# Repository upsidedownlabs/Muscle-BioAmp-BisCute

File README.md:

# Muscle BioAmp BisCute

[-white)](https://store.upsidedownlabs.tech/product/muscle-bioamp-biscute-diy/)

Muscle BioAmp BisCute is a cute DIY EMG sensor for precise ElectroMyoGraphy (EMG) at an affordable cost. It comes with a fixed gain of x2420 and BandPass filter of 72Hz - 720Hz. To record the EMG signals you can use any standalone ADC like ADS1115 or any microcontroller development board with an ADC of your choice like Arduino UNO/Nano.

## Hardware

Muscle BioAmp Biscute has been created using KiCad and all the design files can be found under [hardware](hardware/) folder. Images below shows a quick overview of the hardware design.

| PCB Front           |  PCB Back |
| :-------------------------: | :-------------------------: |
|   |  |

### Assembly

You can get your own Muscle BioAmp BisCute bag of parts from [our store](https://store.upsidedownlabs.tech/product/muscle-bioamp-biscute-diy/) or [Tindie](https://www.tindie.com/products/upsidedownlabs/muscle-bioamp-biscute-diy-muscle-sensor/) and for assembling your Biscute you can take a look at [this interactive BOM](https://upsidedownlabs.github.io/Muscle-BioAmp-BisCute/) or the step by step guide below. 

| Step 1 - Bare board | Step 2 - 100K Resistor | Step 3 - 10K Resistor| Step 4 - 1M Resistor|
| :----: | :----: | :----: | :----: |
| ||||

| Step 5 - 330R Resistor | Step 6 - 220K Resistor | Step 7 - 4.7nF Capacitor | Step 8 - 2.2uF Capacitor |
| :----: | :----: | :----: | :----: |
| ||||

| Step 9 - 470uF Capacitor | Step 10 - 100nF Capacitor | Step 11 - 1nF Capacitor | Step 13 - 1K Resistor |
| :----: | :----: | :----: | :----: |
| ||||

| Step 13 - BioAmp Connector | Step 14 - Header Pin | Step 15 - IC | Step 16 - Biscute ready |
| :----: | :----: | :----: | :----: |
| ||||

## License

| Licenses Facts              |  OSHWA Certification |
| :-------------------------: | :-------------------------: |
|   |  | 

#### Hardware
CERN Open Hardware License Version 2 - Strongly Reciprocal ([CERN-OHL-S-2.0](https://spdx.org/licenses/CERN-OHL-S-2.0.html)).

#### Software
MIT open source [license](http://opensource.org/licenses/MIT).

#### Documentation:
<br />This work is licensed under a <a rel="license" href="http://creativecommons.org/licenses/by/4.0/">Creative Commons Attribution 4.0 International License</a>.

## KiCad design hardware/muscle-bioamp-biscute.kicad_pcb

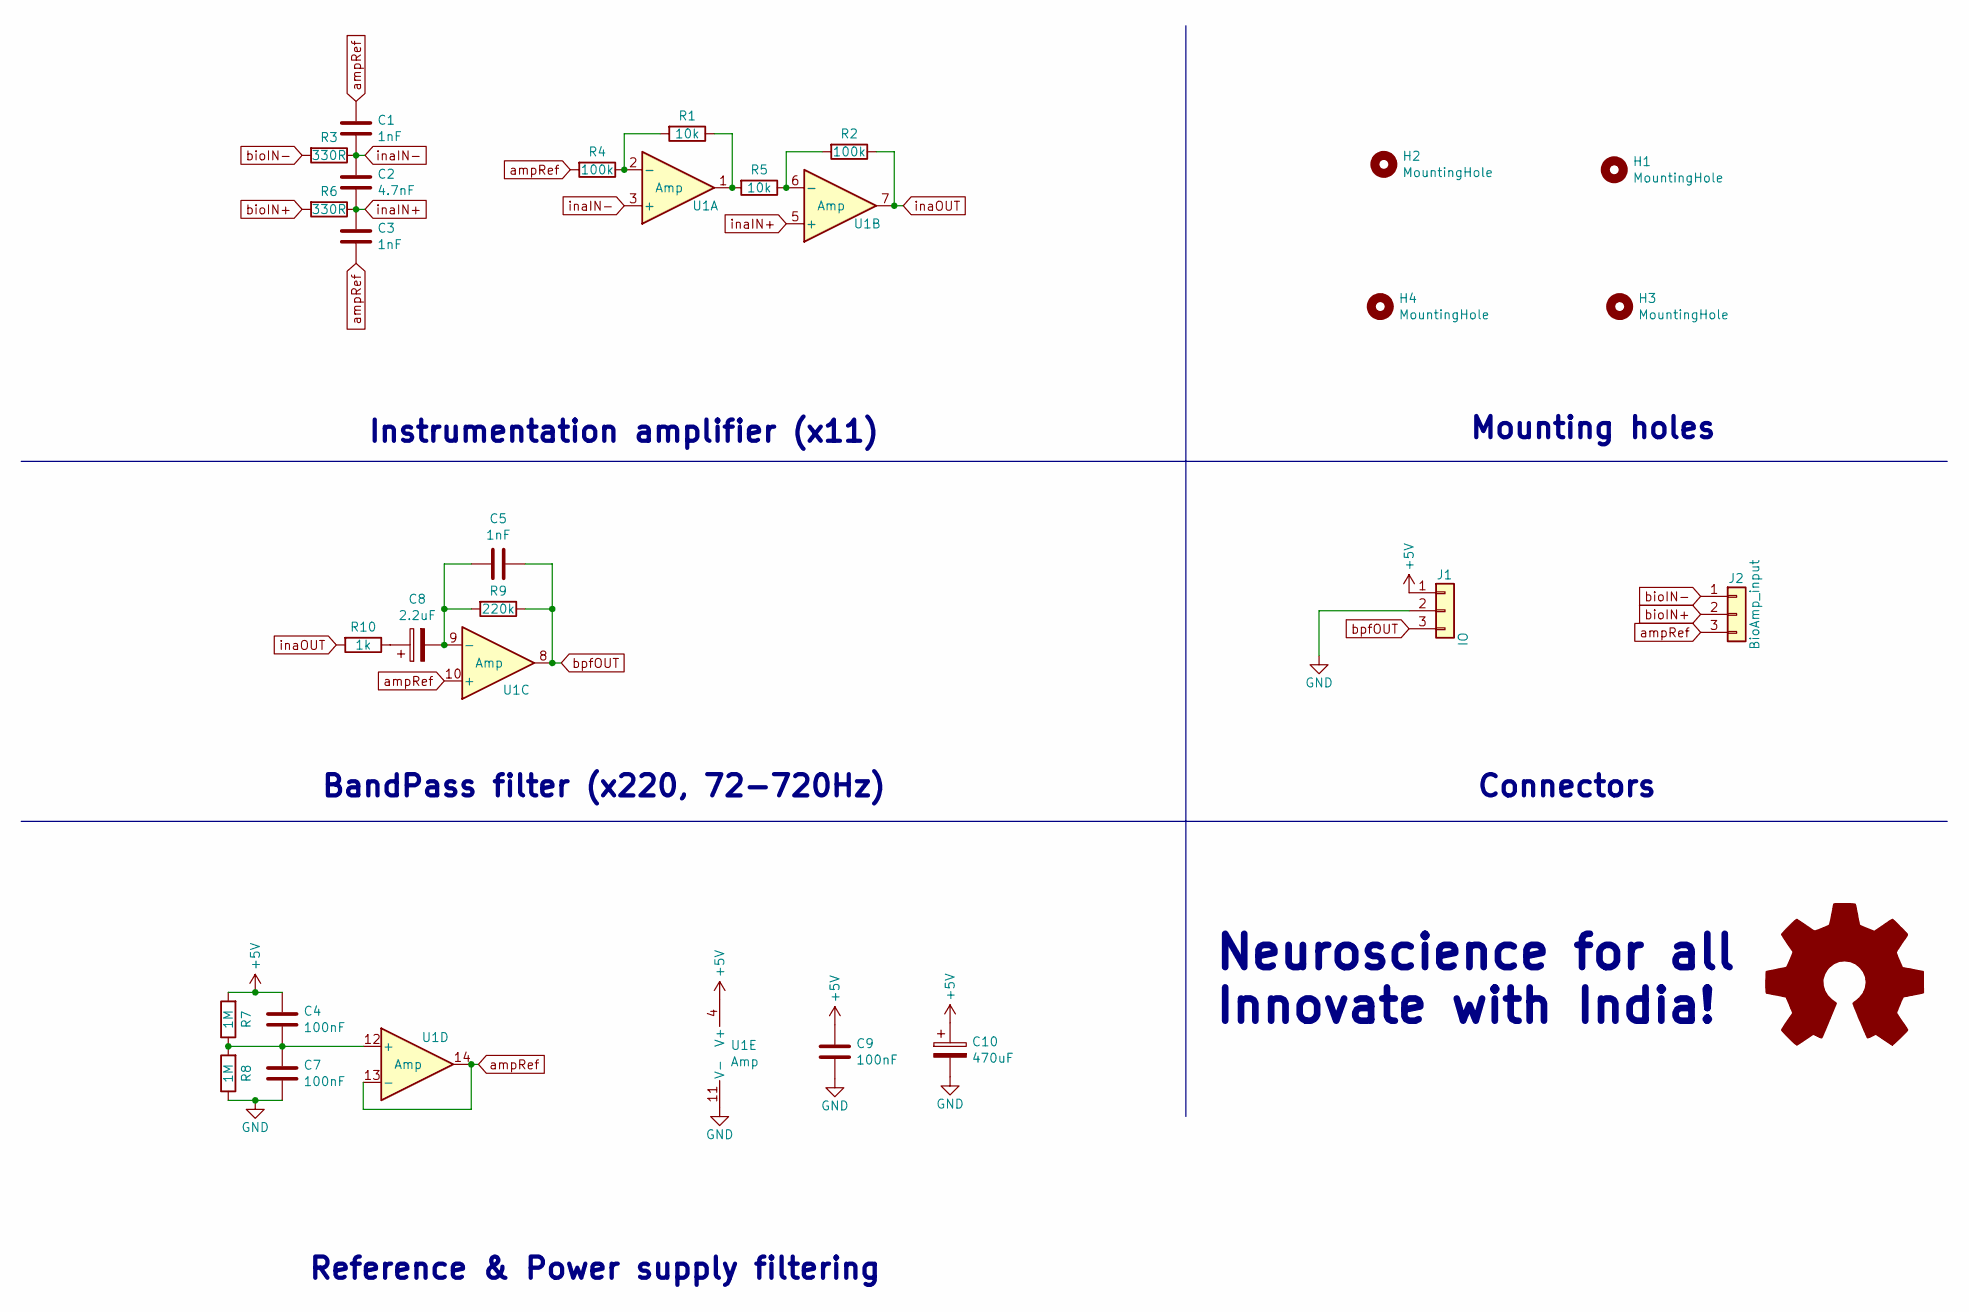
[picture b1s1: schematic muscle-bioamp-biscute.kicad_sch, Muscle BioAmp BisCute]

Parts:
C1, C3, C5: 1nF; C_Disc_D3.8mm_W2.6mm_P2.50mm
C2: 4.7nF; C_Disc_D3.8mm_W2.6mm_P2.50mm
C4, C7, C9: 100nF; C_Disc_D3.8mm_W2.6mm_P2.50mm
C8: 2.2uF; CP_Radial_D5.0mm_P2.50mm
C10: 470uF; CP_Radial_D5.0mm_P2.50mm
H1, H2, H3, H4: MountingHole; MountingHole_2.2mm_M2
J1: IO; PinHeader_1x03_P2.54mm_Vertical
J2: BioAmp_input; JST_PH_B3B-PH-K_1x03_P2.00mm_Vertical
R1, R5: 10k; R_Axial_DIN0207_L6.3mm_D2.5mm_P7.62mm_Horizontal
R2, R4: 100k; R_Axial_DIN0207_L6.3mm_D2.5mm_P7.62mm_Horizontal
R3, R6: 330R; R_Axial_DIN0207_L6.3mm_D2.5mm_P7.62mm_Horizontal
R7, R8: 1M; R_Axial_DIN0207_L6.3mm_D2.5mm_P7.62mm_Horizontal
R9: 220k; R_Axial_DIN0207_L6.3mm_D2.5mm_P7.62mm_Horizontal
R10: 1k; R_Axial_DIN0207_L6.3mm_D2.5mm_P7.62mm_Horizontal
U1: Amp; DIP-14_W7.62mm_LongPads

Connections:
+5V: C4.2, C9.2, C10.1, J1.1, R7.2, U1.4 (V+)
GND: C7.1, C9.1, C10.2, J1.2, R8.1, U1.11 (V-)
unnamed: C4.1, C7.2, R7.1, R8.2, U1.12 (+)
unnamed: C5.1, C8.2, R9.2, U1.9 (-)
unnamed: C8.1, R10.1
unnamed: R1.1, R5.2, U1.1
unnamed: R1.2, R4.1, U1.2 (-)
unnamed: R2.2, R5.1, U1.6 (-)
ampRef: C1.2, C3.1, J2.3, R4.2, U1.10 (+), U1.13 (-), U1.14
bioIN+: J2.2, R6.2
bioIN-: J2.1, R3.2
bpfOUT: C5.2, J1.3, R9.1, U1.8
inaIN+: C2.1, C3.2, R6.1, U1.5 (+)
inaIN-: C1.1, C2.2, R3.1, U1.3 (+)
inaOUT: R2.1, R10.2, U1.7

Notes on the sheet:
Instrumentation amplifier (x11)
Reference & Power supply filtering
Neuroscience for all Innovate with India!
Connectors
BandPass filter (x220, 72-720Hz)
Mounting holes

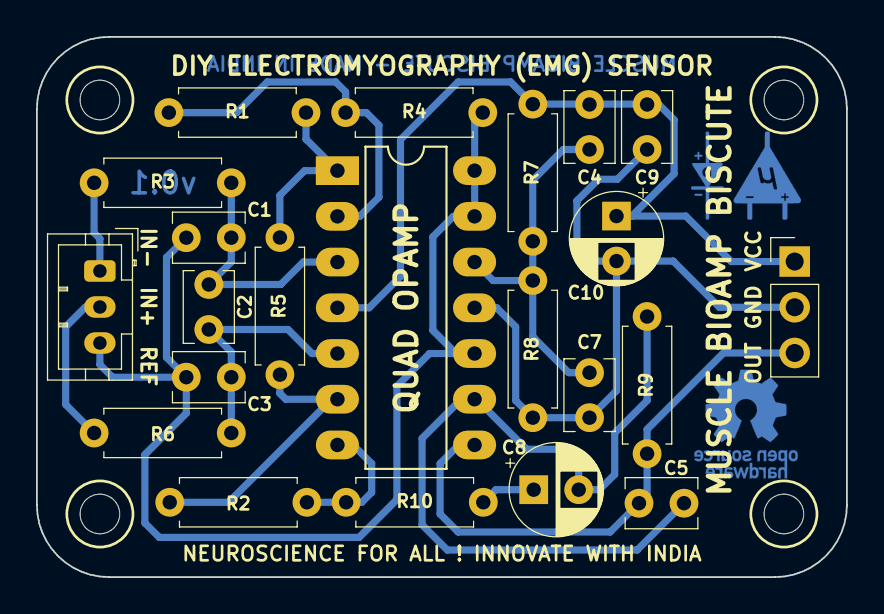
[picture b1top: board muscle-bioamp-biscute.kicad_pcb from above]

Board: 2 copper layers, 45.0 x 30.0 mm, 26 parts (0 on the bottom side), 15 nets.

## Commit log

2022-10-14 Muscle BioAmp BisCute KiCad files
2022-10-14 EMG Envelop example code
2022-10-14 Update license
2022-10-14 Update gitignore
2022-10-14 Add bom/assembly html
2022-10-14 Add board and assembly graphics
2022-10-14 Update board graphics
2022-11-10 Update readme & assembly diagrams
2022-11-10 Update links
2022-11-18 Update images and docs
2022-11-18 Update images
2022-11-18 Fix OSHWA certificate link

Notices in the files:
README.md:
Open Source Licenses Facts  | Open Source Hardware Certification mark
